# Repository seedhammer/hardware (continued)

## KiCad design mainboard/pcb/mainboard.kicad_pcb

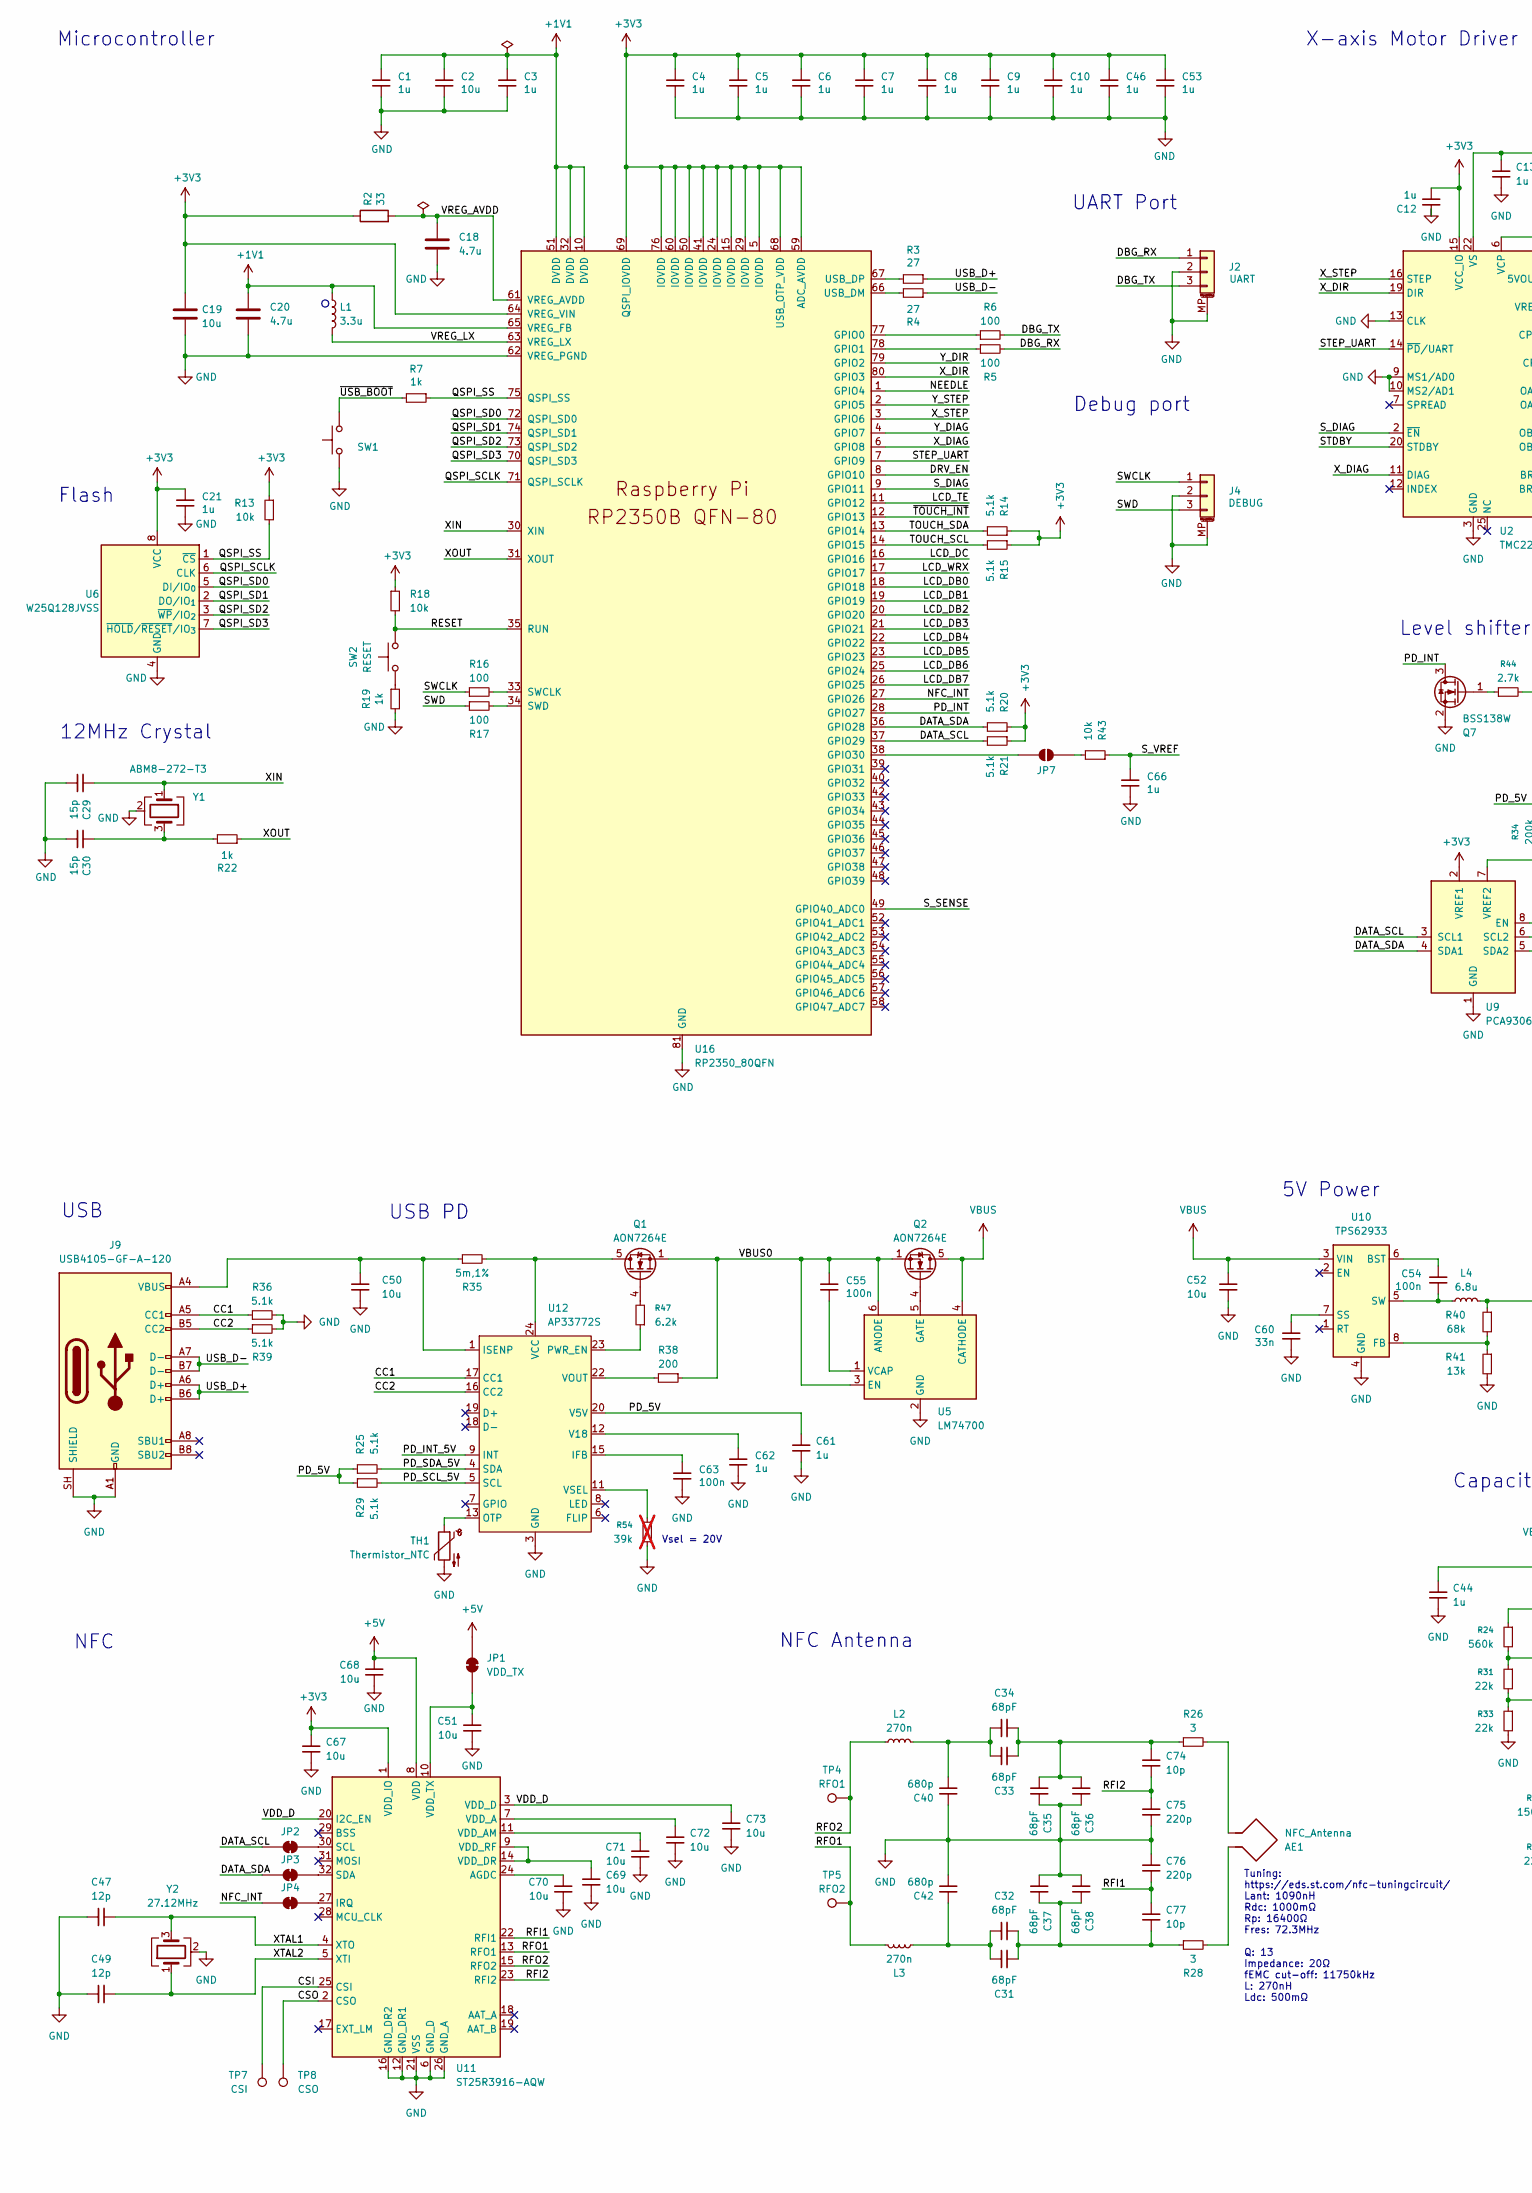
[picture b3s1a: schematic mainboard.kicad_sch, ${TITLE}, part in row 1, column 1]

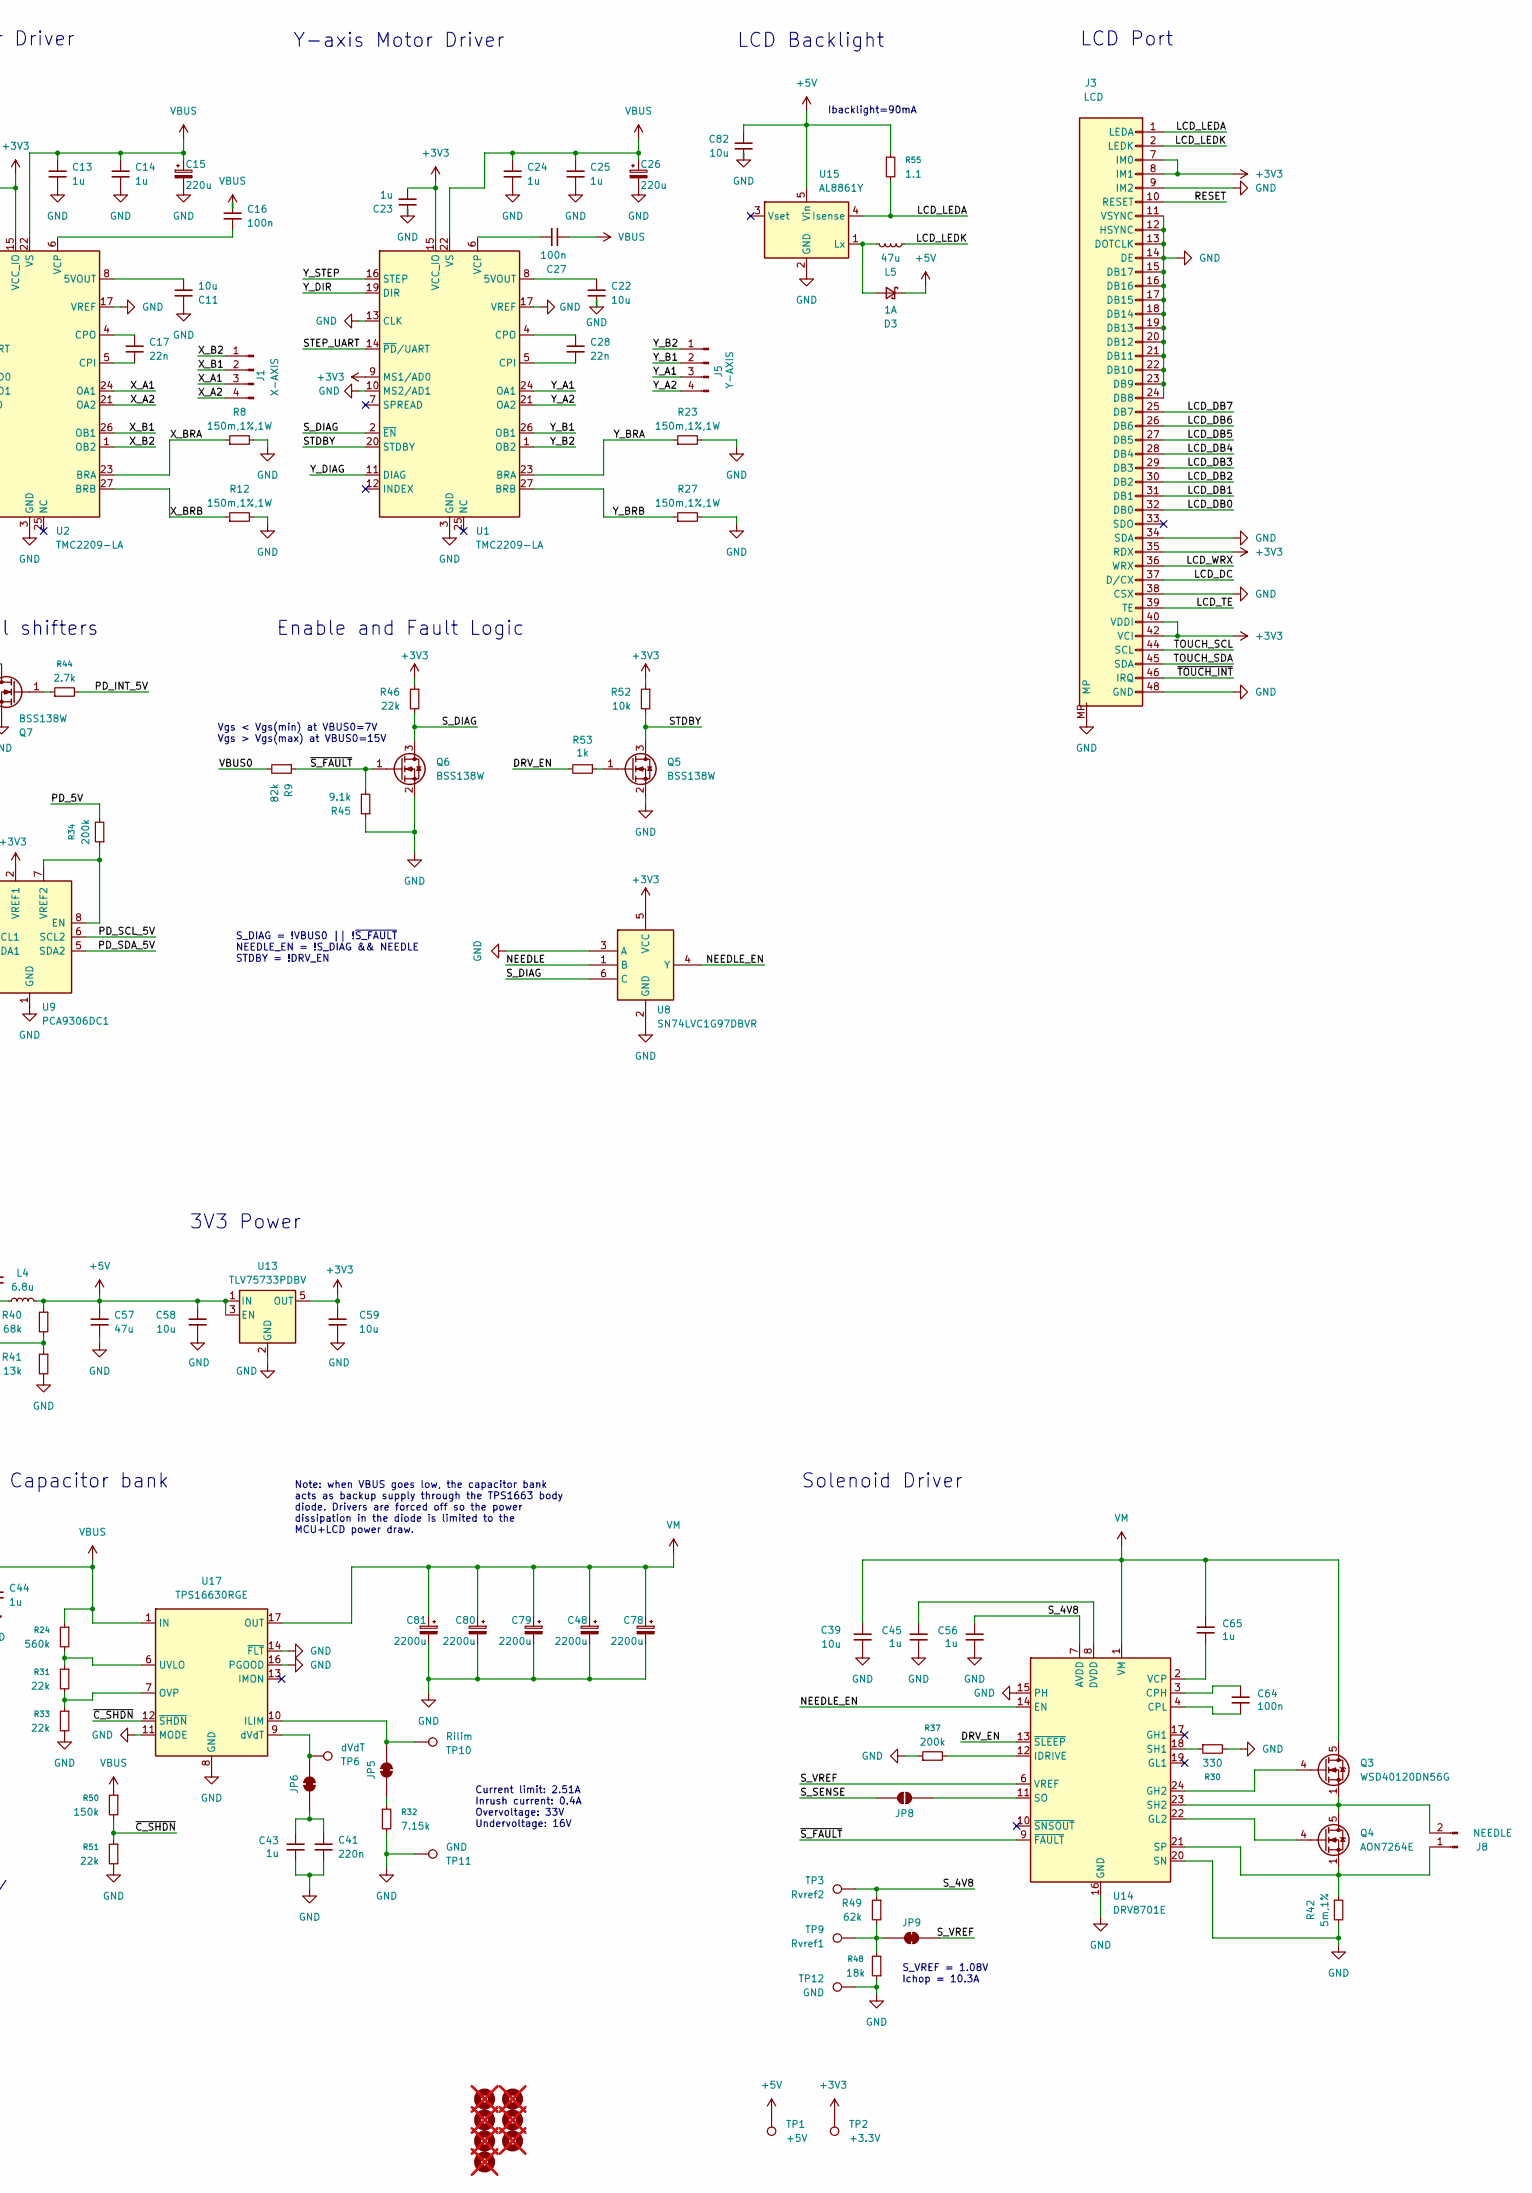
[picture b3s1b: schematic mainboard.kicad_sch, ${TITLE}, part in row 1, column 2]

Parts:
AE1: NFC_Antenna; NFC_Antenna_45x35mm
C1, C3, C4, C5, C6, C7, C8, C9, C10, C12, C21, C23, C43, C45, C46, C53, C56, C61, C62, C65, C66: 1u; C_0402_1005Metric; LCSC C52923
C2, C11, C22, C51, C58, C59, C67, C68, C69, C70, C71, C72, C73, C82: 10u; C_0402_1005Metric; LCSC C15525
C13, C14, C24, C25, C44: 1u; C_0603_1608Metric; LCSC C15849
C15, C26: 220u; CP_Elec_8x10; LCSC C970697
C16, C27: 100n; C_0603_1608Metric; LCSC C14663
C17, C28: 22n; C_0402_1005Metric; LCSC C1532
C18: 4.7u; C_0402_1005Metric; LCSC C23733
C19: 10u; C_0402_1005Metric_small_pads; LCSC C15525
C20: 4.7u; C_0402_1005Metric_small_pads; LCSC C23733
C29, C30: 15p; C_0402_1005Metric; LCSC C1548
C31, C32, C33, C34, C35, C36, C37, C38: 68pF; C_0402_1005Metric; LCSC C389103
C39, C50, C52: 10u; C_1206_3216Metric; LCSC C13585
C40, C42: 680p; C_0402_1005Metric; LCSC C882579
C41: 220n; C_0402_1005Metric; LCSC C16772
C47, C49: 12p; C_0402_1005Metric; LCSC C1547
C48, C78, C79, C80, C81: 2200u; CP_Radial_D13.0mm_P5.00mm; LCSC C7493874
C54, C55, C63, C64: 100n; C_0402_1005Metric; LCSC C307331
C57: 47u; C_1206_3216Metric; LCSC C96123
C60: 33n; C_0603_1608Metric; LCSC C21117
C74, C77: 10p; C_0402_1005Metric; LCSC C161520
C75, C76: 220p; C_0402_1005Metric; LCSC C326765
D3: 1A; D_SOD-323; LCSC C191023
H1, H2, H3, H4, H5, H6, H7: MountingHole; MountingHole_3.2mm_M3_DIN965; not fitted
J1, J5: B4B-XH-2(LF)(SN); JST_XH_B4B-XH-A_1x04_P2.50mm_Vertical_Motor; LCSC C57846
J2, J4: WAFER-SH1.0-3PWB; JST_SH_SM03B-SRSS-TB_1x03-1MP_P1.00mm_Horizontal; LCSC C3029342
J3: AFC07-S50ECC-00; TE_5-1734839-0_1x50-1MP_P0.5mm_Horizontal; LCSC C262650
J8: B2B-XH-A(LF)(SN); JST_XH_B2B-XH-A_1x02_P2.50mm_Vertical; LCSC C24193
J9: USB4105-GF-A-120; USB_C_Receptacle_GCT_USB4105-xx-A_16P_TopMnt_Horizontal; LCSC C5184243
JP1: VDD_TX; SolderJumper-2_P1.3mm_Bridged2Bar_Pad1.0x1.5mm
JP2, JP3, JP4, JP5, JP6: SolderJumper_2_Bridged; SolderJumper-2_P1.3mm_Bridged_Pad1.0x1.5mm
JP7: SolderJumper_2_Bridged; SolderJumper-2_P1.3mm_Open_Pad1.0x1.5mm
JP8: SolderJumper_2_Open; SolderJumper-2_P1.3mm_Open_Pad1.0x1.5mm
JP9: SolderJumper_2_Open; SolderJumper-2_P1.3mm_Bridged_Pad1.0x1.5mm
L1: 3.3u; L_pol_2016; LCSC C42411119
L2, L3: 270n; L_0603_1608Metric; LCSC C2041707
L4: 6.8u; L_Vishay_IFSC-1515AH_4x4x1.8mm; LCSC C843301
L5: 47u; L_Abracon_ASPI-3012S; LCSC C135243
Q1, Q2, Q4: AON7264E; DFN-8-1EP_3x3mm_P0.65mm_EP1.55x2.4mm; LCSC C431191
Q3: WSD40120DN56G; WSD_DFN-8-1EP_6x5mm_P1.27mm_ThermalVias; LCSC C507088
Q5, Q6, Q7: BSS138W; SOT-323_SC-70; LCSC C28646265
R2: 33; R_0402_1005Metric; LCSC C25105
R3, R4: 27; R_0402_1005Metric; LCSC C25100
R5, R6, R16, R17: 100; R_0402_1005Metric; LCSC C25076
R7, R19, R22, R53: 1k; R_0402_1005Metric; LCSC C11702
R8, R12, R23, R27: 150m,1%,1W; R_1206_3216Metric; LCSC C2683383
R9: 82k; R_0603_1608Metric; LCSC C23254
R13, R18, R43, R52: 10k; R_0402_1005Metric; LCSC C25744
R14, R15, R36, R39: 5.1k; R_0402_1005Metric; LCSC C25905
R20, R21, R25, R29: 5.1k; C_0402_1005Metric; LCSC C25905
R24: 560k; R_0603_1608Metric; LCSC C23203
R26, R28: 3; R_0402_1005Metric; LCSC C131555
R30: 330; R_0603_1608Metric; LCSC C23138
R31, R33, R46, R51: 22k; R_0402_1005Metric; LCSC C25768
R32: 7.15k; R_0402_1005Metric; LCSC C409927
R34, R37: 200k; R_0402_1005Metric; LCSC C25764
R35, R42: 5m,1%; R_0805_2012Metric; LCSC C728267
R38: 200; R_0402_1005Metric; LCSC C25087
R40: 68k; R_0603_1608Metric; LCSC C23231
R41: 13k; R_0603_1608Metric; LCSC C22797
R44: 2.7k; R_0603_1608Metric; LCSC C13167
R45: 9.1k; R_0603_1608Metric; LCSC C23260
R47: 6.2k; R_0603_1608Metric; LCSC C4260
R48: 18k; R_0603_1608Metric; LCSC C25810
R49: 62k; R_0603_1608Metric; LCSC C23221
R50: 150k; R_0603_1608Metric; LCSC C22807
R54: 39k; R_0603_1608Metric; LCSC C23153; not fitted
R55: 1.1; R_0402_1005Metric; LCSC C11803
SW1, SW2: TS3425BA; SW_Push_1P1T_NO_Vertical_Wuerth_434133025816; LCSC C2681476
TH1: Thermistor_NTC; R_0402_1005Metric; LCSC C77131
TP1: +5V; TestPoint_Pad_1.5x1.5mm
TP2: +3.3V; TestPoint_Pad_1.5x1.5mm
TP3: Rvref2; TestPoint_THTPad_1.5x1.5mm_Drill0.7mm
TP4: RFO1; TestPoint_Pad_D1.0mm
TP5: RFO2; TestPoint_Pad_D1.0mm
TP6: dVdT; TestPoint_THTPad_1.5x1.5mm_Drill0.7mm
TP7: CSI; TestPoint_Pad_1.0x1.0mm
TP8: CSO; TestPoint_Pad_1.0x1.0mm
TP9: Rvref1; TestPoint_THTPad_1.5x1.5mm_Drill0.7mm
TP10: Rilim; TestPoint_THTPad_1.5x1.5mm_Drill0.7mm
TP11, TP12: GND; TestPoint_THTPad_1.5x1.5mm_Drill0.7mm
U1, U2: TMC2209-LA; VQFN-28-1EP_5x5mm_P0.5mm_EP3.7x3.7mm_ThermalVias; LCSC C2150710
U5: LM74700; SOT-23-6; LCSC C2941042
U6: W25Q128JVSS; SOIC-8_5.3x5.3mm_P1.27mm; LCSC C97521
U8: SN74LVC1G97DBVR; SOT-23-6; LCSC C128411
U9: PCA9306DC1; VSSOP-8_2.3x2mm_P0.5mm; LCSC C33196
U10: TPS62933; SOT-583-8; LCSC C3200405
U11: ST25R3916-AQW; VQFN-32-1EP_5x5mm_P0.5mm_EP3.5x3.5mm_ThermalVias; LCSC C2908147
U12: AP33772S; QFN-24-1EP_4x4mm_P0.5mm_EP2.7x2.7mm_ThermalVias; LCSC C9900152998
U13: TLV75733PDBV; SOT-23-5; LCSC C485517
U14: DRV8701E; VQFN-24-1EP_4x4mm_P0.5mm_EP2.45x2.45mm_ThermalVias; LCSC C90964
U15: AL8861Y; SOT-89-5; LCSC C507867
U16: RP2350_80QFN; QFN-80-1EP_10x10mm_P0.4mm_EP3.4x3.4mm_ThermalVias; LCSC C42415655
U17: TPS16630RGE; Texas_RGE0024H_VQFN-24-1EP_4x4mm_P0.5mm_EP2.7x2.7mm_Thermal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; LCSC C1850279
Y1: ABM8-272-T3; Crystal_SMD_3225-4Pin_3.2x2.5mm; LCSC C20625731
Y2: 27.12MHz; Crystal_SMD_3225-4Pin_3.2x2.5mm; LCSC C251622

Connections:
+1V1: C1.1, C2.1, C3.1, C20.1, L1.1, U16.10 (DVDD), U16.32 (DVDD), U16.51 (DVDD), U16.65 (VREG_FB)
+3V3: C4.1, C5.1, C6.1, C7.1, C8.1, C9.1, C10.1, C12.2, C19.1, C21.1, C23.2, C46.1, C53.1, C59.1, C67.1, J3.7 (IM0), J3.8 (IM1), J3.35 (RDX), J3.40 (VDDI), J3.41 (VDDI), J3.42 (VCI), R2.1, R13.1, R14.1, R15.1, R18.1, R20.1, R21.1, R46.1, R52.1, TP2.1 (1_1), U1.9 (MS1/AD0), U1.15 (VCC_IO), U2.15 (VCC_IO), U6.8 (VCC), U8.5 (VCC), U9.2 (VREF1), U11.1 (VDD_IO), U13.5 (OUT), U16.5 (IOVDD), U16.15 (IOVDD), U16.24 (IOVDD), U16.29 (IOVDD), U16.41 (IOVDD), U16.50 (IOVDD), U16.59 (ADC_AVDD), U16.60 (IOVDD), U16.64 (VREG_VIN), U16.68 (USB_OTP_VDD), U16.69 (QSPI_IOVDD), U16.76 (IOVDD)
+5V: C57.1, C58.1, C68.1, C82.1, D3.1 (K), JP1.2 (B), L4.2, R40.1, R55.1, TP1.1 (1_1), U11.8 (VDD), U13.1 (IN), U13.3 (EN), U15.5 (Vin)
/CC1: J9.A5 (CC1), R36.1, U12.17 (CC1)
/CC2: J9.B5 (CC2), R39.1, U12.16 (CC2)
/CSI: TP7.1 (1_1), U11.25 (CSI)
/CSO: TP8.1 (1_1), U11.2 (CSO)
/DATA_SCL: JP2.1 (A), R21.2, U9.3 (SCL1), U16.37 (GPIO29)
/DATA_SDA: JP3.1 (A), R20.2, U9.4 (SDA1), U16.36 (GPIO28)
/DBG_RX: J2.1, R5.2
/DBG_TX: J2.3, R6.2
/DRV_EN: R53.2, U14.13 (~SLEEP), U16.8 (GPIO10)
/LCD_DB0: J3.32 (DB0), U16.18 (GPIO18)
/LCD_DB1: J3.31 (DB1), U16.19 (GPIO19)
/LCD_DB2: J3.30 (DB2), U16.20 (GPIO20)
/LCD_DB3: J3.29 (DB3), U16.21 (GPIO21)
/LCD_DB4: J3.28 (DB4), U16.22 (GPIO22)
/LCD_DB5: J3.27 (DB5), U16.23 (GPIO23)
/LCD_DB6: J3.26 (DB6), U16.25 (GPIO24)
/LCD_DB7: J3.25 (DB7), U16.26 (GPIO25)
/LCD_DC: J3.37 (D/CX), U16.16 (GPIO16)
/LCD_LEDA: J3.1 (LEDA), R55.2, U15.4 (Isense)
/LCD_LEDK: J3.2 (LEDK), J3.3 (LEDK), L5.1
/LCD_TE: J3.39 (TE), U16.11 (GPIO12)
/LCD_WRX: J3.36 (WRX), U16.17 (GPIO17)
/NEEDLE: U8.1 (B), U16.1 (GPIO4)
/NEEDLE_EN: U8.4 (Y), U14.14 (EN)
/NFC_INT: JP4.1 (A), U16.27 (GPIO26)
/PD_5V: C61.1, R25.1, R29.1, R34.2, U12.20 (V5V)
/PD_INT: Q7.3 (D), U16.28 (GPIO27)
/PD_INT_5V: R44.2, U12.9 (INT)
/PD_SCL_5V: R29.2, U9.6 (SCL2), U12.5 (SCL)
/PD_SDA_5V: R25.2, U9.5 (SDA2), U12.4 (SDA)
/QSPI_SCLK: U6.6 (CLK), U16.71 (QSPI_SCLK)
/QSPI_SD0: U6.5 (DI/IO_{0}), U16.72 (QSPI_SD0)
/QSPI_SD1: U6.2 (DO/IO_{1}), U16.74 (QSPI_SD1)
/QSPI_SD2: U6.3 (~WP/IO_{2}), U16.73 (QSPI_SD2)
/QSPI_SD3: U6.7 (~HOLD/~RESET/IO_{3}), U16.70 (QSPI_SD3)
/QSPI_SS: R7.1, R13.2, U6.1 (~CS), U16.75 (QSPI_SS)
/RESET: J3.10 (RESET), J3.47 (RST), R18.2, SW2.2, U16.35 (RUN)
/RFI1: C76.2, C77.1, U11.22 (RFI1)
/RFI2: C74.2, C75.1, U11.23 (RFI2)
/RFO1: L3.1, TP5.1 (1_1), U11.13 (RFO1)
/RFO2: L2.1, TP4.1 (1_1), U11.15 (RFO2)
/STDBY: Q5.3 (D), R52.2, U1.20 (STDBY), U2.20 (STDBY)
/STEP_UART: U1.14 (~PD/UART), U2.14 (~PD/UART), U16.7 (GPIO9)
/SWCLK: J4.1, R16.1
/SWD: J4.3, R17.1
/S_4V8: C56.1, R49.1, TP3.1 (1_1), U14.7 (AVDD)
/S_DIAG: Q6.3 (D), R46.2, U1.2 (~EN), U2.2 (~EN), U8.6 (C), U16.9 (GPIO11)
/S_SENSE: JP8.1 (A), U16.49 (GPIO40_ADC0)
/S_VREF: C66.1, JP9.2 (B), R43.1, U14.6 (VREF)
/TOUCH_SCL: J3.44 (SCL), R15.2, U16.14 (GPIO15)
/TOUCH_SDA: J3.45 (SDA), R14.2, U16.13 (GPIO14)
/USB_D+: J9.A6 (D+), J9.B6 (D+), R3.1
/USB_D-: J9.A7 (D-), J9.B7 (D-), R4.1
/VBUS0: C55.1, Q1.1 (S), Q1.2 (S), Q1.3 (S), Q2.1 (S), Q2.2 (S), Q2.3 (S), R9.2, R38.1, U5.3 (EN), U5.6 (ANODE)
/VDD_D: C73.1, U11.3 (VDD_D), U11.20 (I2C_EN)
/VREG_AVDD: C18.1, R2.2, U16.61 (VREG_AVDD)
/VREG_LX: L1.2, U16.63 (VREG_LX)
/XIN: C29.1, U16.30 (XIN), Y1.1
/XOUT: R22.1, U16.31 (XOUT)
/XTAL1: C47.1, U11.4 (XTO), Y2.3
/XTAL2: C49.1, U11.5 (XTI), Y2.1
/X_A1: J1.3, U2.24 (OA1)
/X_A2: J1.4, U2.21 (OA2)
/X_B1: J1.2, U2.26 (OB1)
/X_B2: J1.1, U2.1 (OB2)
/X_BRA: R8.1, U2.23 (BRA)
/X_BRB: R12.1, U2.27 (BRB)
/X_DIAG: U2.11 (DIAG), U16.6 (GPIO8)
/X_DIR: U2.19 (DIR), U16.80 (GPIO3)
/X_STEP: U2.16 (STEP), U16.3 (GPIO6)
/Y_A1: J5.3, U1.24 (OA1)
/Y_A2: J5.4, U1.21 (OA2)
/Y_B1: J5.2, U1.26 (OB1)
/Y_B2: J5.1, U1.1 (OB2)
/Y_BRA: R23.1, U1.23 (BRA)
/Y_BRB: R27.1, U1.27 (BRB)
/Y_DIAG: U1.11 (DIAG), U16.4 (GPIO7)
/Y_DIR: U1.19 (DIR), U16.79 (GPIO2)
/Y_STEP: U1.16 (STEP), U16.2 (GPIO5)
/~C_SHDN: R50.2, R51.1, U17.12 (~SHDN)
/~S_FAULT: Q6.1 (G), R9.1, R45.2, U14.9 (~FAULT)
/~TOUCH_INT: J3.46 (IRQ), U16.12 (GPIO13)
/~USB_BOOT: R7.2, SW1.1
GND: C1.2, C2.2, C3.2, C4.2, C5.2, C6.2, C7.2, C8.2, C9.2, C10.2, C11.1, C12.1, C13.2, C14.2, C15.2, C18.2, C19.2, C20.2, C21.2, C22.2, C23.1, C24.2, C25.2, C26.2, C29.2, C30.2, C35.1, C36.1, C37.2, C38.2, C39.2, C40.1, C41.2, C42.2, C43.2, C44.2, C45.2, C46.2, C47.2, C48.2, C49.2, C50.2, C51.2, C52.2, C53.2, C56.2, C57.2, C58.2, C59.2, C60.2, C61.2, C62.2, C63.2, C66.2, C67.2, C68.2, C69.2, C70.2, C71.2, C72.2, C73.2, C75.2, C76.1, C78.2, C79.2, C80.2, C81.2, C82.2, J2.2, J2.MP (MountPin), J3.9 (IM2), J3.11 (VSYNC), J3.12 (HSYNC), J3.13 (DOTCLK), J3.14 (DE), J3.15 (DB17), J3.16 (DB16), J3.17 (DB15), J3.18 (DB14), J3.19 (DB13), J3.20 (DB12), J3.21 (DB11), J3.22 (DB10), J3.23 (DB9), J3.24 (DB8), J3.34 (SDA), J3.38 (CSX), J3.43 (GND), J3.48 (GND), J3.49 (GND), J3.50 (GND), J3.MP, J4.2, J4.MP (MountPin), J9.A1 (GND), J9.A12 (GND), J9.B1 (GND), J9.B12 (GND), J9.SH (SHIELD), Q5.2 (S), Q6.2 (S), Q7.2 (S), R8.2, R12.2, R19.2, R23.2, R27.2, R30.2, R32.2, R33.2, R36.2, R37.1, R39.2, R41.2, R42.2, R45.1, R48.1, R51.2, SW1.2, TH1.2, TP11.1 (1_1), TP12.1 (1_1), U1.3 (GND), U1.10 (MS2/AD1), U1.13 (CLK), U1.17 (VREF), U1.18 (GND), U1.29 (GND), U2.3 (GND), U2.9 (MS1/AD0), U2.10 (MS2/AD1), U2.13 (CLK), U2.17 (VREF), U2.18 (GND), U2.29 (GND), U5.2 (GND), U6.4 (GND), U8.2 (GND), U8.3 (A), U9.1 (GND), U10.4 (GND), U11.6 (GND_D), U11.12 (GND_DR1), U11.16 (GND_DR2), U11.21 (VSS), U11.26 (GND_A), U11.33 (EP), U12.3 (GND), U12.25 (GND), U13.2 (GND), U14.5 (GND), U14.15 (PH), U14.16 (GND), U14.20 (SN), U14.25 (GND), U15.2 (GND), U16.62 (VREG_PGND), U16.81 (GND), U17.8 (GND), U17.11 (MODE), U17.14 (~FLT), U17.16 (PGOOD), U17.19 (NC), U17.20 (NC), U17.21 (NC), U17.22 (NC), U17.23 (NC), U17.24 (NC), U17.25 (GND), Y1.2 (G), Y1.4 (G), Y2.2 (G), Y2.4 (G)
unnamed: AE1.1, R28.2
unnamed: AE1.2, R26.2
unnamed: C30.1, R22.2, Y1.3
unnamed: C31.1, C32.1, C42.1, L3.2
unnamed: C31.2, C32.2, C37.1, C38.1, C77.2, R28.1
unnamed: C33.1, C34.1, C40.2, L2.2
unnamed: C33.2, C34.2, C35.2, C36.2, C74.1, R26.1
unnamed: D3.2 (A), L5.2, U15.1 (Lx)
unnamed: J8.1, Q4.1 (S), Q4.2 (S), Q4.3 (S), R42.1, U14.21 (SP)
unnamed: J8.2, Q3.1 (S), Q3.2 (S), Q3.3 (S), Q4.5 (D), Q4.6 (D), Q4.7 (D), Q4.8 (D), Q4.9 (D), U14.23 (SH2)
unnamed: C51.1, JP1.1 (A), U11.10 (VDD_TX)
unnamed: JP2.2 (B), U11.30 (SCL)
unnamed: JP3.2 (B), U11.32 (SDA)
unnamed: JP4.2 (B), U11.27 (IRQ)
unnamed: JP5.1 (A), R32.1
unnamed: JP5.2 (B), TP10.1 (1_1), U17.10 (ILIM)
unnamed: C41.1, C43.1, JP6.1 (A)
unnamed: JP6.2 (B), TP6.1 (1_1), U17.9 (dVdT)
unnamed: JP7.1 (A), R43.2
unnamed: JP7.2 (B), U16.38 (GPIO30)
unnamed: JP8.2 (B), U14.11 (SO)
unnamed: JP9.1 (A), R48.2, R49.2, TP9.1 (1_1)
unnamed: Q1.4 (G), R47.2
unnamed: Q2.4 (G), U5.5 (GATE)
unnamed: Q3.4 (G), U14.24 (GH2)
unnamed: Q4.4 (G), U14.22 (GL2)
unnamed: Q5.1 (G), R53.1
unnamed: Q7.1 (G), R44.1
unnamed: R19.1, SW2.1
unnamed: C22.1, U1.8 (5VOUT)
unnamed: C28.2, U1.5 (CPI)
unnamed: C28.1, U1.4 (CPO)
unnamed: C27.1, U1.6 (VCP)
unnamed: C11.2, U2.8 (5VOUT)
unnamed: C17.2, U2.5 (CPI)
unnamed: C17.1, U2.4 (CPO)
unnamed: C16.2, U2.6 (VCP)
unnamed: C55.2, U5.1 (VCAP)
unnamed: R34.1, U9.7 (VREF2), U9.8 (EN)
unnamed: C54.1, U10.6 (BST)
unnamed: R40.2, R41.1, U10.8 (FB)
unnamed: C60.1, U10.7 (SS)
unnamed: C54.2, L4.1, U10.5 (SW)
unnamed: C70.1, U11.24 (AGDC)
unnamed: C72.1, U11.7 (VDD_A)
unnamed: C71.1, U11.11 (VDD_AM)
unnamed: C69.1, U11.9 (VDD_RF), U11.14 (VDD_DR)
unnamed: C63.1, U12.15 (IFB)
unnamed: C50.1, J9.A4 (VBUS), J9.A9 (VBUS), J9.B4 (VBUS), J9.B9 (VBUS), R35.1, U12.1 (ISENP)
unnamed: TH1.1, U12.13 (OTP)
unnamed: R47.1, U12.23 (PWR_EN)
unnamed: C62.1, U12.12 (V18)
unnamed: Q1.5 (D), Q1.6 (D), Q1.7 (D), Q1.8 (D), Q1.9 (D), R35.2, U12.24 (VCC)
unnamed: R38.2, U12.22 (VOUT)
unnamed: R54.1, U12.11 (VSEL)
unnamed: C64.1, U14.3 (CPH)
unnamed: C64.2, U14.4 (CPL)
unnamed: C45.1, U14.8 (DVDD)
unnamed: R37.2, U14.12 (IDRIVE)
unnamed: R30.1, U14.18 (SH1)
unnamed: C65.2, U14.2 (VCP)
unnamed: R6.1, U16.77 (GPIO0)
unnamed: R5.1, U16.78 (GPIO1)
unnamed: R16.2, U16.33 (SWCLK)
unnamed: R17.2, U16.34 (SWD)
unnamed: R4.2, U16.66 (USB_DM)
unnamed: R3.2, U16.67 (USB_DP)
unnamed: R31.2, R33.1, U17.7 (OVP)
unnamed: R24.2, R31.1, U17.6 (UVLO)
VBUS: C13.1, C14.1, C15.1, C16.1, C24.1, C25.1, C26.1, C27.2, C44.1, C52.1, Q2.5 (D), Q2.6 (D), Q2.7 (D), Q2.8 (D), Q2.9 (D), R24.1, R50.1, U1.22 (VS), U1.28 (VS), U2.22 (VS), U2.28 (VS), U5.4 (CATHODE), U10.3 (VIN), U17.1 (IN), U17.2 (IN), U17.5 (P_IN)
VM: C39.1, C48.1, C65.1, C78.1, C79.1, C80.1, C81.1, Q3.5 (D), U14.1 (VM), U17.17 (OUT), U17.18 (OUT)

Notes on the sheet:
LCD Port
S_VREF = 1.08V Ichop = 10.3A
Capacitor bank
UART Port
USB
NFC Antenna
Level shifters
X-axis Motor Driver
Solenoid Driver
USB PD
Current limit: 2.51A Inrush current: 0.4A Overvoltage: 33V Undervoltage: 16V
Note: when VBUS goes low, the capacitor bank acts as backup supply through the TPS1663 body diode. Drivers are forced off so the power dissipation in the diode is limited to the MCU+LCD power draw.
Tuning: https://eds.st.com/nfc-tuningcircuit/ Lant: 1090nH Rdc: 1000mΩ Rp: 16400Ω Fres: 72.3MHz Q: 13 Impedance: 20Ω fEMC cut-off: 11750kHz L: 270nH Ldc: 500mΩ
Vsel = 20V
LCD Backlight
NFC
5V Power
Debug port
Y-axis Motor Driver
Vgs < Vgs(min) at VBUS0=7V Vgs > Vgs(max) at VBUS0=15V
S_DIAG = !VBUS0 || !~{S_FAULT} NEEDLE_EN = !S_DIAG && NEEDLE STDBY = !DRV_EN
Microcontroller
Ibacklight=90mA
12MHz Crystal
3V3 Power
Flash
Enable and Fault Logic

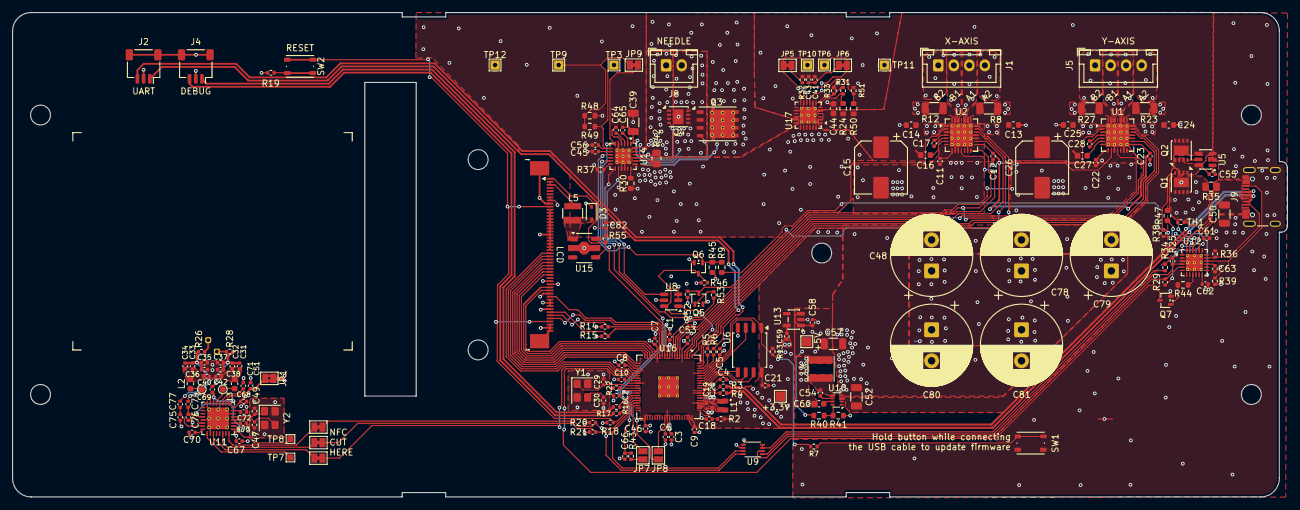
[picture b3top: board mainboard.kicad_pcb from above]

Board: 4 copper layers, 205.3 x 78.0 mm, 201 parts (1 on the bottom side), 157 nets.
